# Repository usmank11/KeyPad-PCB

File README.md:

# KeyPad-PCB
KeyPad-PCB

4 Mechanical key switch PCB using ATMEGA32U4 Microchip.

PCB Front

PCB Back

Schematic

Layout

**Components used:**
<br />
ATMEGA32U4:
https://www.digikey.ca/en/products/detail/microchip-technology/ATMEGA32U4-AUR/2238241

FA-238 Crystal:
https://www.digikey.ca/en/products/detail/epson/FA-238-16-0000MB-C3/2403378

Diodes:
https://www.digikey.ca/en/products/detail/micro-commercial-co/1N4148W-TP/717196

Button:
https://www.digikey.ca/en/products/detail/e-switch/TL3342F160QG-TR/379003

22 Ohm Resistors:
https://www.digikey.ca/en/products/detail/stackpole-electronics-inc/RMCF0805JT22R0/1757897

10k Ohm Resistors:
https://www.digikey.ca/en/products/detail/stackpole-electronics-inc/RMCF0805JT10K0/1757762

22pF Capacitors:
https://www.digikey.ca/en/products/detail/kemet/C0805C220J5GAC7800/411112

0.1uF Capacitors:
https://www.digikey.ca/en/products/detail/yageo/CC0805ZRY5V9BB104/2103099

1uF Capacitors:
https://www.digikey.ca/en/products/detail/yageo/CC0805KKX7R7BB105/2103103

4.7uF Capacitors:
https://www.digikey.ca/en/products/detail/kyocera-avx/08055D475KAT2A/13557255

Mini USB Connector:
https://www.digikey.ca/en/products/detail/hirose-electric-co-ltd/UX60SC-MB-5S8/1949202

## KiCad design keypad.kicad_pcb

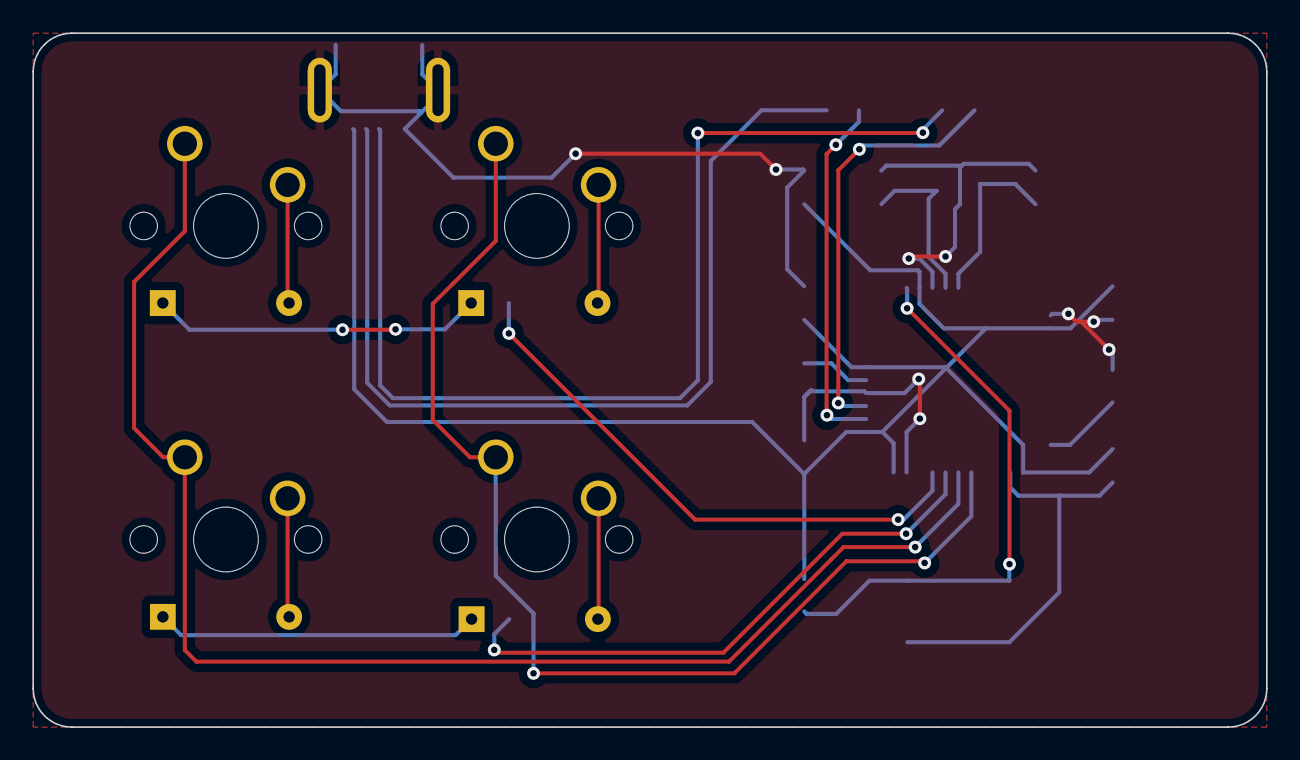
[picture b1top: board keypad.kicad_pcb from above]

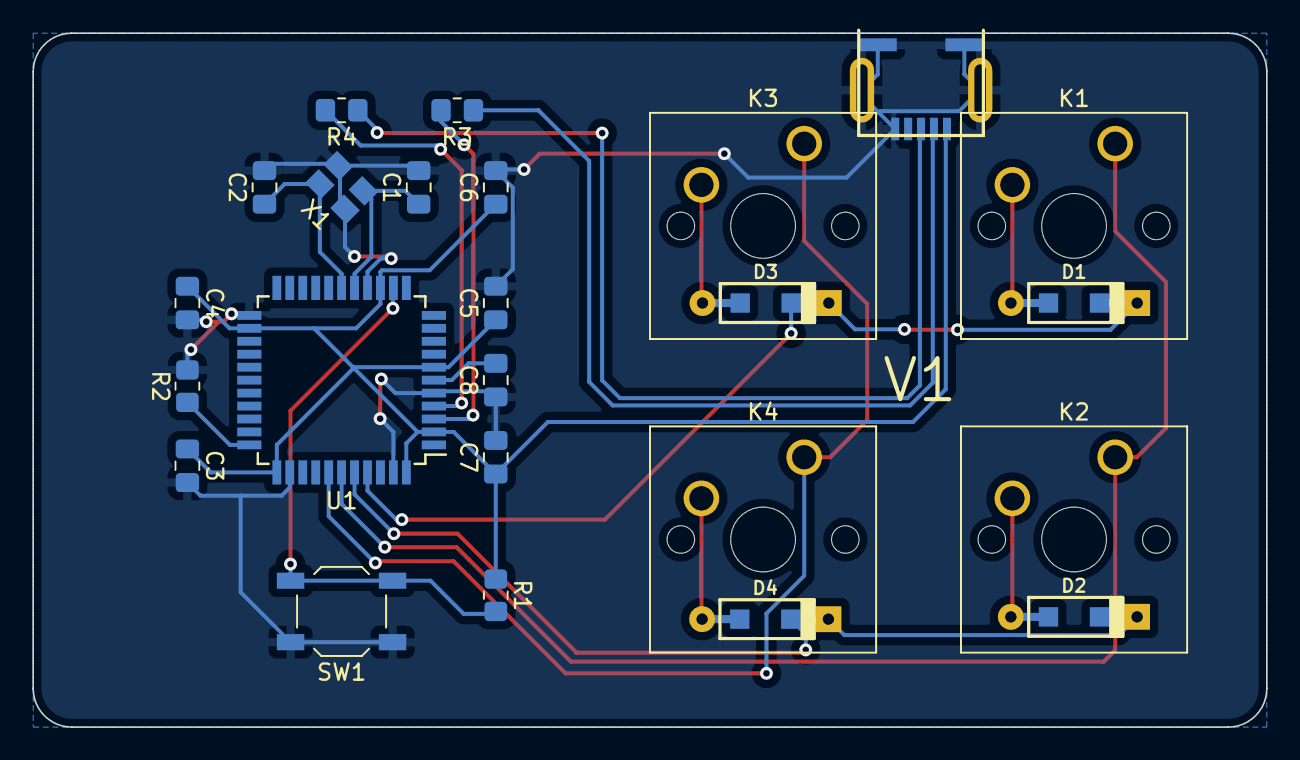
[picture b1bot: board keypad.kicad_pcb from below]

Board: 2 copper layers, 76.2 x 42.9 mm, 24 parts (24 on the bottom side), 19 nets.

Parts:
C1, C2: 22p; C_0805_2012Metric_Pad1.18x1.45mm_HandSolder
C3, C4, C5, C6: 0.1u; C_0805_2012Metric_Pad1.18x1.45mm_HandSolder
C7: 4.7u; C_0805_2012Metric_Pad1.18x1.45mm_HandSolder
C8: 1u; C_0805_2012Metric_Pad1.18x1.45mm_HandSolder
D1, D2, D3, D4: 12; D_SOD123_axial
J1: USB_mini_micro_B; USB_miniB_hirose_5S8
K1, K2, K3, K4: KEYSW; SW_Cherry_MX_1.00u_PCB
R1, R2: 10k; R_0805_2012Metric_Pad1.20x1.40mm_HandSolder
R3, R4: 22; R_0805_2012Metric_Pad1.20x1.40mm_HandSolder
SW1: SW_PUSH; SW_SPST_TL3342
U1: ATMEGA32U4; TQFP-44_10x10mm_P0.8mm
X1: XTAL_GND; crystal_FA238-TSX3225

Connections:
/col0: K1.1, K2.1, U1.39 (PF4)
/col1: K3.1, K4.1, U1.38 (PF5)
/row0: D1.1 (K), D3.1 (K), U1.41 (PF0)
/row1: D2.1 (K), D4.1 (K), U1.40 (PF1)
GND: C1.2, C2.2, C3.2, C4.2, C5.2, C6.2, C7.2, C8.1, J1.5 (GND), J1.6 (SHIELD), R2.2, SW1.1, U1.5 (UGnd), U1.15 (GND), U1.23 (GND), U1.35 (GND), U1.43 (GND), X1.3
unnamed: C1.1, U1.16 (XTAL1), X1.1
unnamed: C2.1, U1.17 (XTAL2), X1.2
unnamed: C8.2, U1.6 (UCap)
unnamed: D1.2 (A), K1.2
unnamed: D2.2 (A), K2.2
unnamed: D3.2 (A), K3.2
unnamed: D4.2 (A), K4.2
unnamed: J1.2 (D-), R3.1
unnamed: J1.3 (D+), R4.1
unnamed: R1.2, SW1.2, U1.13 (~RESET)
unnamed: R2.1, U1.33 (~HWB/PE2)
unnamed: R3.2, U1.3 (D-)
unnamed: R4.2, U1.4 (D+)
VCC: C3.1, C4.1, C5.1, C6.1, C7.1, J1.1 (VUSB), R1.1, U1.2 (UVcc), U1.7 (VBus), U1.14 (VCC), U1.24 (AVCC), U1.34 (VCC), U1.44 (AVCC)
